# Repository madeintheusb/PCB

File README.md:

# PCB
Eagle Cad PCB developed for MadeInThsUSB

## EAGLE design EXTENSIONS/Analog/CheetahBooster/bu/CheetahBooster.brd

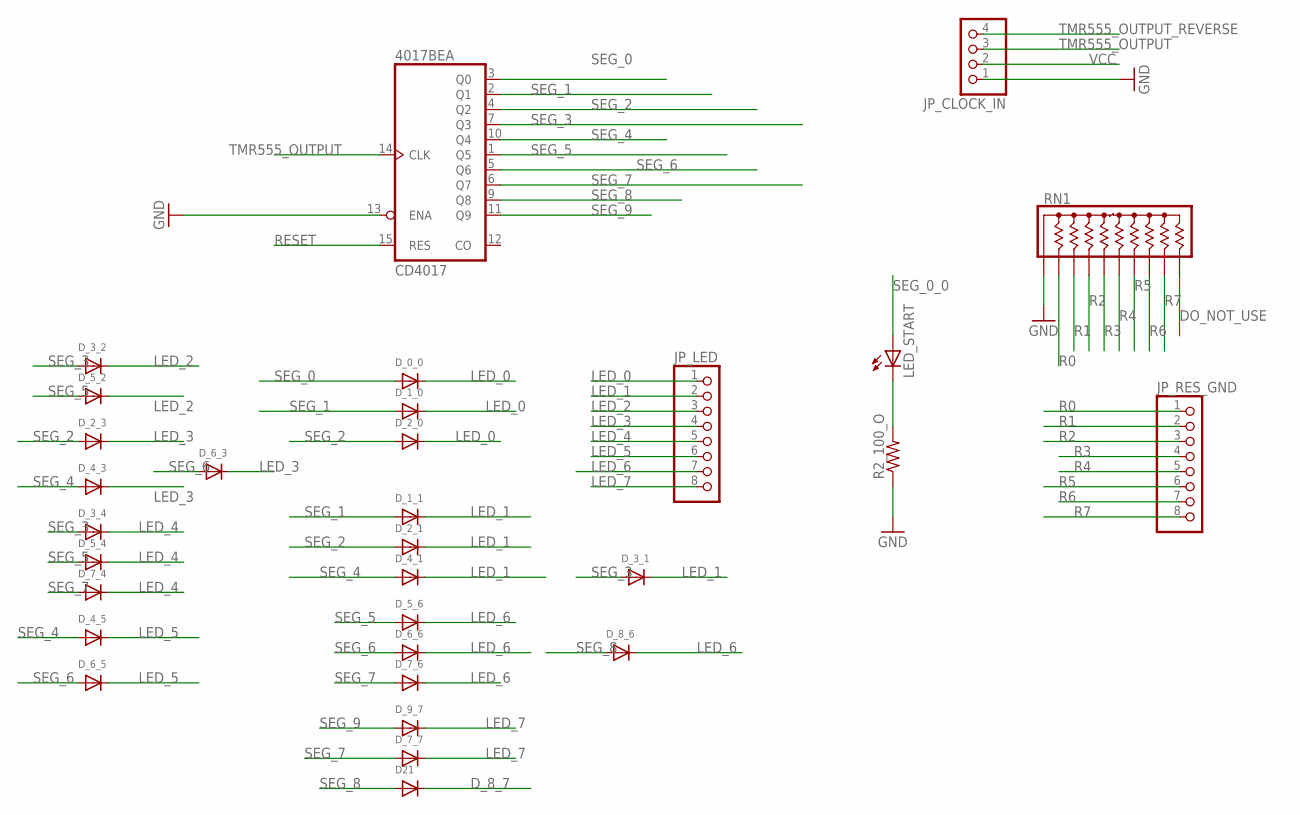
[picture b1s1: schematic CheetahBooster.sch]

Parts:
4017BE: CD4017; DIL16
D21: DIODESMA; SMADIODE
D_0_0, D_1_0, D_1_1, D_2_0, D_2_1, D_2_3, D_3_1, D_3_2, D_3_4, D_4_1, D_4_3, D_4_5, D_5_2, D_5_4, D_5_6, D_6_3, D_6_5, D_6_6, D_7_4, D_7_6, D_7_7, D_8_6, D_9_7: DIODESMA; SMADIODE
JP_CLOCK_IN: PINHD-1X4; 1X04
JP_LED: PINHD-1X8; 1X08
JP_RES_GND: PINHD-1X8; 1X08
LED_START: LEDSMT1206; 1206
R2_100_O: R-US_R1206; R1206
RN1: 4610X; SIP10

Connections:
DO_NOT_USE: RN1.10
D_8_7: D21.C
GND: 4017BE.8 (GND), 4017BE.13 (ENA), JP_CLOCK_IN.1, R2_100_O.1, RN1.1
LED_0: D_0_0.C, D_1_0.C, D_2_0.C, JP_LED.1
LED_1: D_1_1.C, D_2_1.C, D_3_1.C, D_4_1.C, JP_LED.2
LED_2: D_3_2.C, D_5_2.C, JP_LED.3
LED_3: D_2_3.C, D_4_3.C, D_6_3.C, JP_LED.4
LED_4: D_3_4.C, D_5_4.C, D_7_4.C, JP_LED.5
LED_5: D_4_5.C, D_6_5.C, JP_LED.6
LED_6: D_5_6.C, D_6_6.C, D_7_6.C, D_8_6.C, JP_LED.7
LED_7: D_7_7.C, D_9_7.C, JP_LED.8
unnamed: LED_START.C, R2_100_O.2
R0: JP_RES_GND.1, RN1.2
R1: JP_RES_GND.2, RN1.3
R2: JP_RES_GND.3, RN1.4
R3: JP_RES_GND.4, RN1.5
R4: JP_RES_GND.5, RN1.6
R5: JP_RES_GND.6, RN1.7
R6: JP_RES_GND.7, RN1.8
R7: JP_RES_GND.8, RN1.9
RESET: 4017BE.15 (RES)
SEG_0: 4017BE.3 (Q0), D_0_0.A
SEG_0_0: LED_START.A
SEG_1: 4017BE.2 (Q1), D_1_0.A, D_1_1.A
SEG_2: 4017BE.4 (Q2), D_2_0.A, D_2_1.A, D_2_3.A
SEG_3: 4017BE.7 (Q3), D_3_1.A, D_3_2.A, D_3_4.A
SEG_4: 4017BE.10 (Q4), D_4_1.A, D_4_3.A, D_4_5.A
SEG_5: 4017BE.1 (Q5), D_5_2.A, D_5_4.A, D_5_6.A
SEG_6: 4017BE.5 (Q6), D_6_3.A, D_6_5.A, D_6_6.A
SEG_7: 4017BE.6 (Q7), D_7_4.A, D_7_6.A, D_7_7.A
SEG_8: 4017BE.9 (Q8), D21.A, D_8_6.A
SEG_9: 4017BE.11 (Q9), D_9_7.A
TMR555_OUTPUT: 4017BE.14 (CLK), JP_CLOCK_IN.3
TMR555_OUTPUT_REVERSE: JP_CLOCK_IN.4
VCC: 4017BE.16 (VCC), JP_CLOCK_IN.2

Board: 2 copper layers, 31 parts (0 on the bottom side), 30 nets, no tracks yet.

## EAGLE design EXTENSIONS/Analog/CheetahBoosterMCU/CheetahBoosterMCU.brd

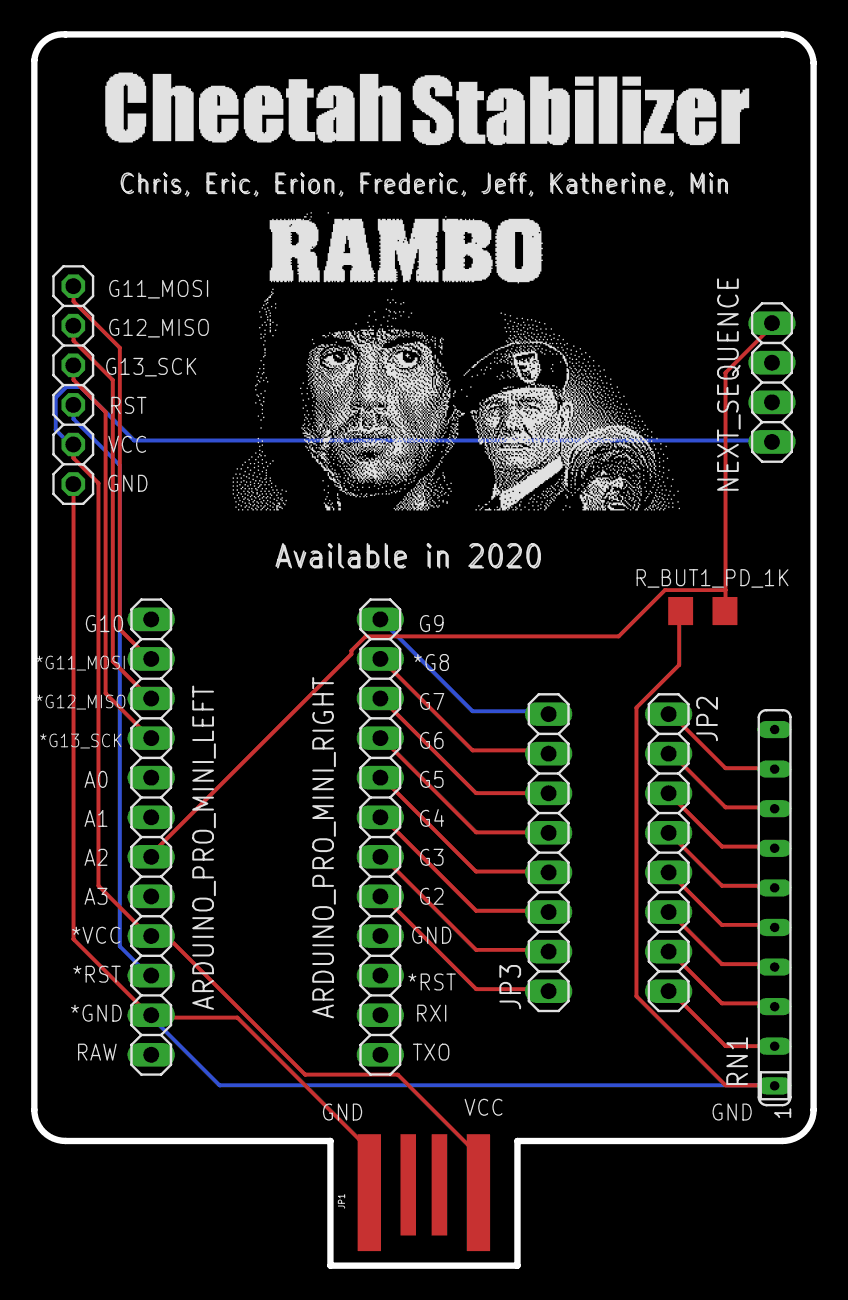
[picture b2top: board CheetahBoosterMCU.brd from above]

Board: 2 copper layers, 50.0 x 79.0 mm, 9 parts (0 on the bottom side), 23 nets.

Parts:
ARDUINO_PRO_MINI_LEFT: 1X12
ARDUINO_PRO_MINI_RIGHT: 1X12
JP1: USBPCB; USB-A-PCB
JP2, JP3: 1X08
JP_PROGRAMMING: 1X06
NEXT_SEQUENCE: 1X04
RN1: SIP10
R_BUT1_PD_1K: R1206

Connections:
A2: ARDUINO_PRO_MINI_LEFT.7, NEXT_SEQUENCE.4, R_BUT1_PD_1K.2
G2: ARDUINO_PRO_MINI_RIGHT.8, JP3.1
G3: ARDUINO_PRO_MINI_RIGHT.7, JP3.2
G4: ARDUINO_PRO_MINI_RIGHT.6, JP3.3
G5: ARDUINO_PRO_MINI_RIGHT.5, JP3.4
G6: ARDUINO_PRO_MINI_RIGHT.4, JP3.5
G7: ARDUINO_PRO_MINI_RIGHT.3, JP3.6
G8: ARDUINO_PRO_MINI_RIGHT.2, JP3.7
G9: ARDUINO_PRO_MINI_RIGHT.1, JP3.8
G11_MOSI: ARDUINO_PRO_MINI_LEFT.2, JP_PROGRAMMING.6
G12_MISO: ARDUINO_PRO_MINI_LEFT.3, JP_PROGRAMMING.5
G13_SCK: ARDUINO_PRO_MINI_LEFT.4, JP_PROGRAMMING.4
GND: ARDUINO_PRO_MINI_LEFT.11, JP1.GND, JP_PROGRAMMING.1, RN1.1, R_BUT1_PD_1K.1
R0: JP2.1, RN1.9
R1: JP2.2, RN1.8
R2: JP2.3, RN1.7
R3: JP2.4, RN1.6
R4: JP2.5, RN1.5
R5: JP2.6, RN1.4
R6: JP2.7, RN1.3
R7: JP2.8, RN1.2
RST: ARDUINO_PRO_MINI_LEFT.10, JP_PROGRAMMING.3
VCC: ARDUINO_PRO_MINI_LEFT.9, JP1.5V, JP_PROGRAMMING.2, NEXT_SEQUENCE.1

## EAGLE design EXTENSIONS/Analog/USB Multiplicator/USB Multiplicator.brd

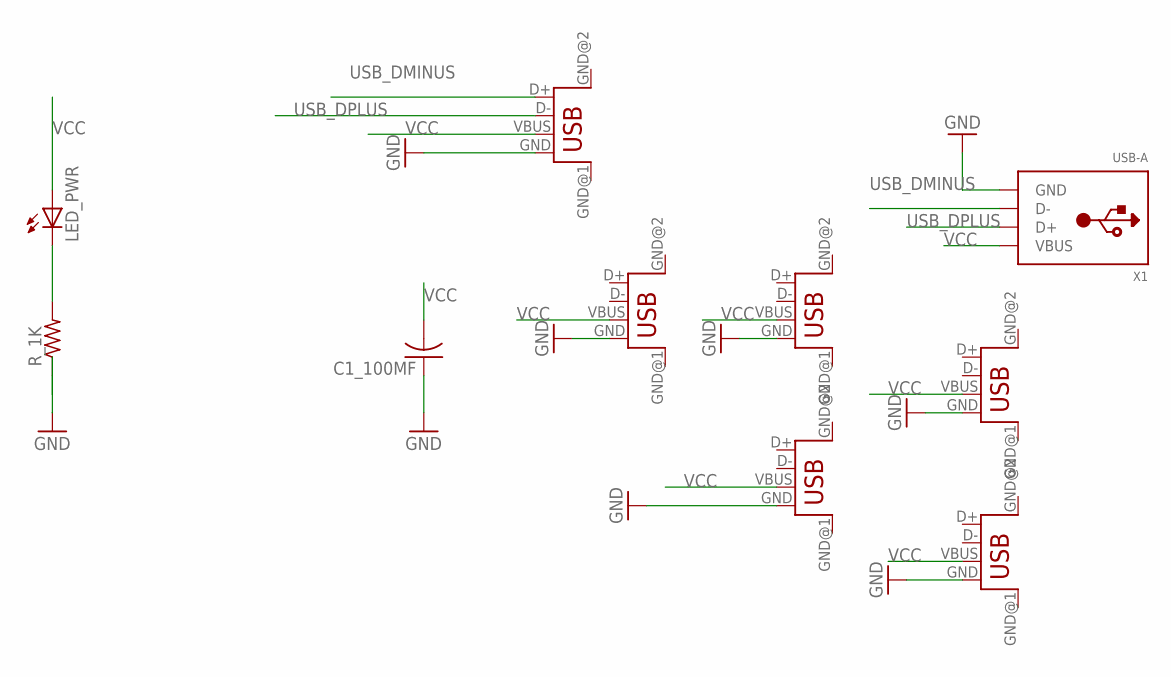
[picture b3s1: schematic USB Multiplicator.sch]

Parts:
C1_100MF: C-US025-030X050; C025-030X050
LED_PWR: LEDSMT1206; 1206
R_1K: R-US_R1206; R1206
USB_OUT_2, USB_OUT_3, USB_OUT_4, USB_OUT_5, USB_OUT_6: USB; USB-FEMALE-A-PTH
USB_OUT_WITH_DATA_1: USB; USB-FEMALE-A-PTH
X1: USB-A; MOLEX_480371000

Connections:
GND: C1_100MF.1, R_1K.1, USB_OUT_2.GND, USB_OUT_3.GND, USB_OUT_4.GND, USB_OUT_5.GND, USB_OUT_6.GND, USB_OUT_WITH_DATA_1.GND, X1.4 (GND)
unnamed: LED_PWR.C, R_1K.2
USB_DMINUS: USB_OUT_WITH_DATA_1.D+, X1.2 (D-)
USB_DPLUS: USB_OUT_WITH_DATA_1.D-, X1.3 (D+)
VCC: C1_100MF.2, LED_PWR.A, USB_OUT_2.VBUS, USB_OUT_3.VBUS, USB_OUT_4.VBUS, USB_OUT_5.VBUS, USB_OUT_6.VBUS, USB_OUT_WITH_DATA_1.VBUS, X1.1 (VBUS)

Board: 2 copper layers, 10 parts (0 on the bottom side), 5 nets, no tracks yet.

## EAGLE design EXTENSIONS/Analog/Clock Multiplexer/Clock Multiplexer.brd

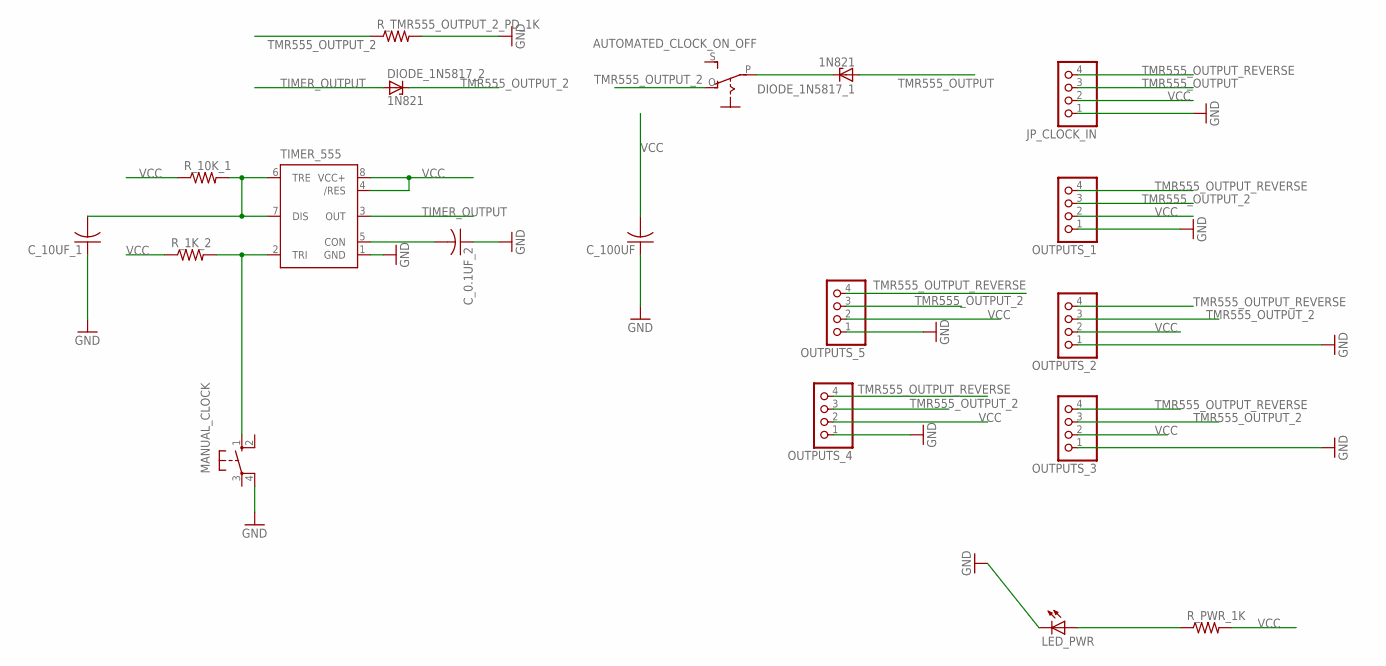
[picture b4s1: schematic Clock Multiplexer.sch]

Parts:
AUTOMATED_CLOCK_ON_OFF: EG1218S; EG1218
C_0.1UF_2, C_10UF_1: C-USC1206; C1206
C_100UF: C-US025-030X050; C025-030X050
DIODE_1N5817_1, DIODE_1N5817_2: 1N821; DO35Z10
JP_CLOCK_IN: PINHD-1X4; 1X04
LED_PWR: LEDSMT1206; 1206
MANUAL_CLOCK: 10-XX; B3F-10XX
OUTPUTS_1, OUTPUTS_2, OUTPUTS_3, OUTPUTS_4, OUTPUTS_5: PINHD-1X4; 1X04
R_1K_2, R_10K_1: R-US_R1206; R1206
R_PWR_1K: R-US_R1206; R1206
R_TMR555_OUTPUT_2_PD_1K: R-US_R1206; R1206
TIMER_555: NE555D; SO08

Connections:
GND: C_0.1UF_2.1, C_10UF_1.1, C_100UF.1, JP_CLOCK_IN.1, LED_PWR.C, MANUAL_CLOCK.4 (P1), OUTPUTS_1.1, OUTPUTS_2.1, OUTPUTS_3.1, OUTPUTS_4.1, OUTPUTS_5.1, R_TMR555_OUTPUT_2_PD_1K.2, TIMER_555.1 (GND)
unnamed: LED_PWR.A, R_PWR_1K.1
unnamed: AUTOMATED_CLOCK_ON_OFF.P, DIODE_1N5817_1.C
unnamed: C_10UF_1.2, R_10K_1.2, TIMER_555.6 (TRE), TIMER_555.7 (DIS)
unnamed: C_0.1UF_2.2, TIMER_555.5 (CON)
unnamed: MANUAL_CLOCK.1 (S), R_1K_2.2, TIMER_555.2 (TRI)
TIMER_OUTPUT: DIODE_1N5817_2.A, TIMER_555.3 (OUT)
TMR555_OUTPUT: DIODE_1N5817_1.A, JP_CLOCK_IN.3
TMR555_OUTPUT_2: AUTOMATED_CLOCK_ON_OFF.O, DIODE_1N5817_2.C, OUTPUTS_1.3, OUTPUTS_2.3, OUTPUTS_3.3, OUTPUTS_4.3, OUTPUTS_5.3, R_TMR555_OUTPUT_2_PD_1K.1
TMR555_OUTPUT_REVERSE: JP_CLOCK_IN.4, OUTPUTS_1.4, OUTPUTS_2.4, OUTPUTS_3.4, OUTPUTS_4.4, OUTPUTS_5.4
VCC: C_100UF.2, JP_CLOCK_IN.2, OUTPUTS_1.2, OUTPUTS_2.2, OUTPUTS_3.2, OUTPUTS_4.2, OUTPUTS_5.2, R_1K_2.1, R_10K_1.1, R_PWR_1K.2, TIMER_555.4 (/RES), TIMER_555.8 (VCC+)

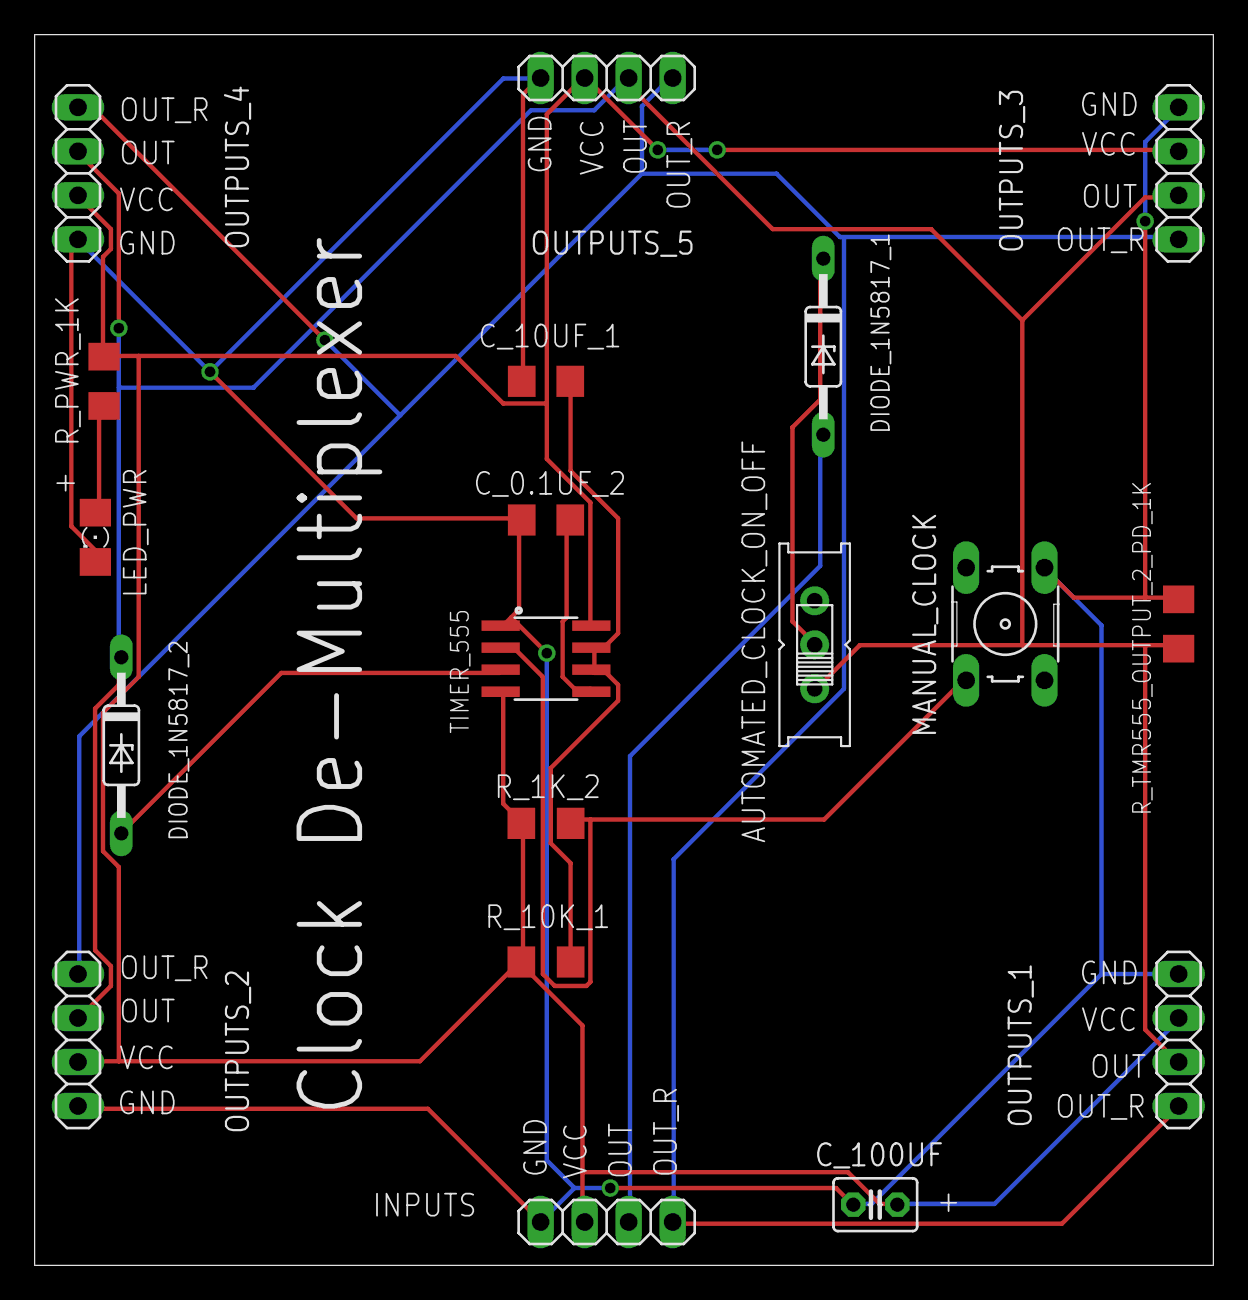
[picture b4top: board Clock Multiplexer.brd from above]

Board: 2 copper layers, 68.0 x 71.0 mm, 19 parts (0 on the bottom side), 11 nets.

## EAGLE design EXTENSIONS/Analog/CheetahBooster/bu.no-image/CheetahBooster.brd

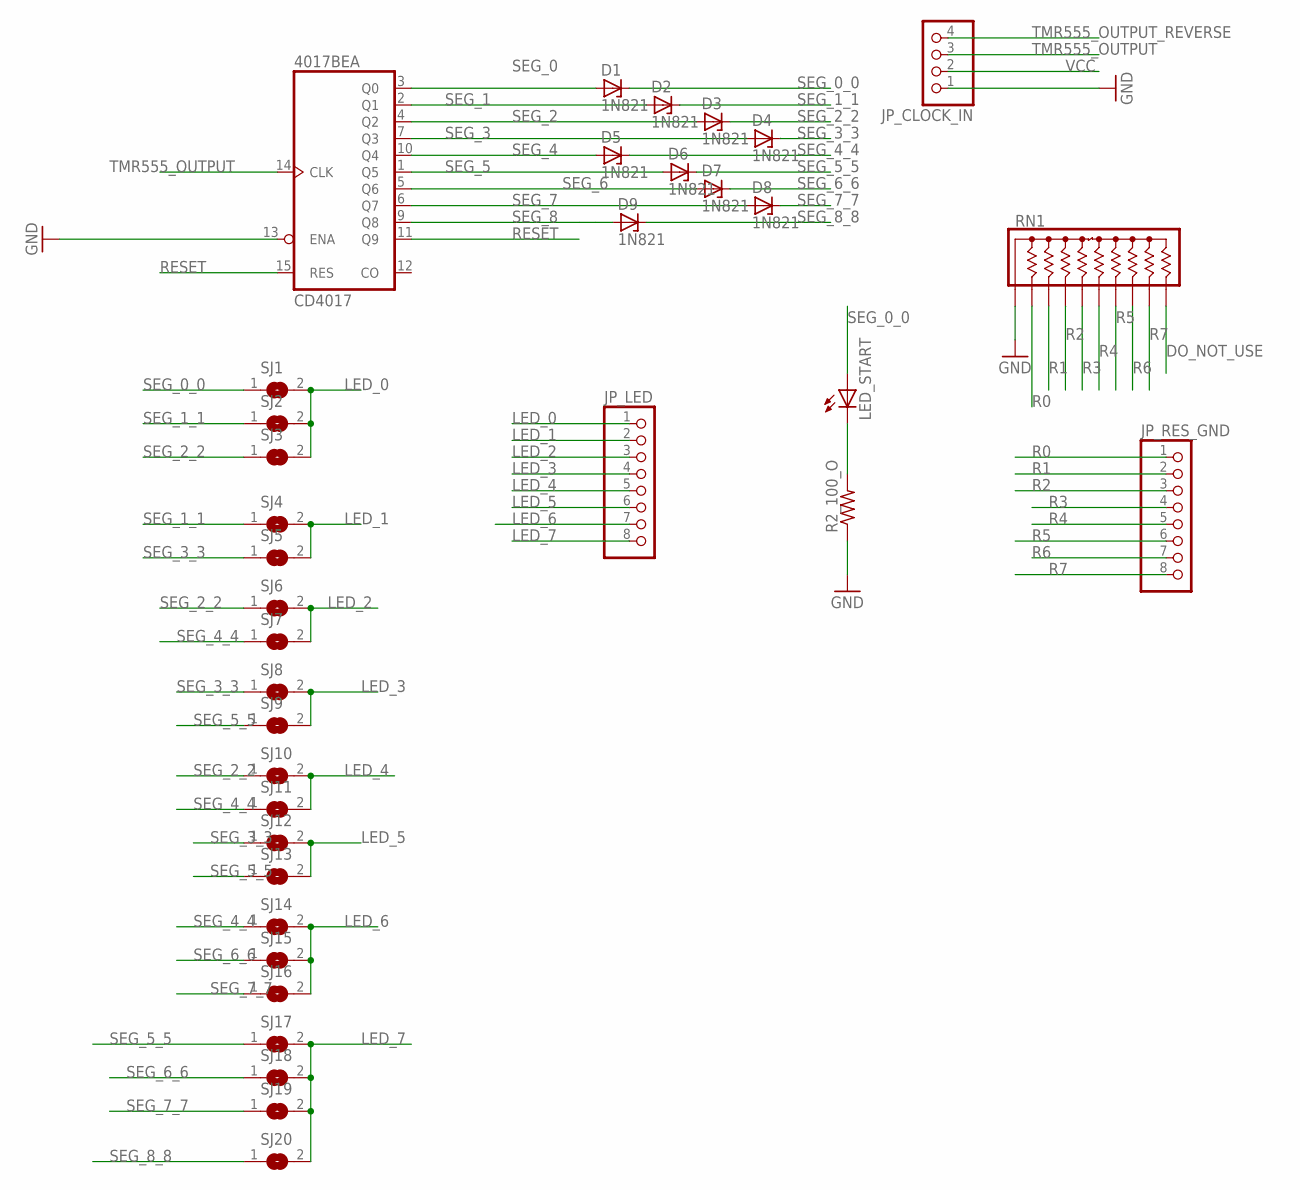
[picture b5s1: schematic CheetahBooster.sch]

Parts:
4017BE: CD4017; DIL16
D1, D2, D3, D4, D5, D6, D7, D8, D9: 1N821; DO35Z10
JP_CLOCK_IN: PINHD-1X4; 1X04
JP_LED: PINHD-1X8; 1X08
JP_RES_GND: PINHD-1X8; 1X08
LED_START: LEDSMT1206; 1206
R2_100_O: R-US_R1206; R1206
RN1: 4610X; SIP10
SJ1, SJ2, SJ3, SJ4, SJ5, SJ6, SJ7, SJ8, SJ9, SJ10, SJ11, SJ12, SJ13, SJ14, SJ15, SJ16, SJ17, SJ18, SJ19, SJ20: SOLDERJUMPER; SOLDERJUMPER_ARROW_NOPASTE

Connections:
DO_NOT_USE: RN1.10
GND: 4017BE.8 (GND), 4017BE.13 (ENA), JP_CLOCK_IN.1, R2_100_O.1, RN1.1
LED_0: JP_LED.1, SJ1.2, SJ2.2, SJ3.2
LED_1: JP_LED.2, SJ4.2, SJ5.2
LED_2: JP_LED.3, SJ6.2, SJ7.2
LED_3: JP_LED.4, SJ8.2, SJ9.2
LED_4: JP_LED.5, SJ10.2, SJ11.2
LED_5: JP_LED.6, SJ12.2, SJ13.2
LED_6: JP_LED.7, SJ14.2, SJ15.2, SJ16.2
LED_7: JP_LED.8, SJ17.2, SJ18.2, SJ19.2, SJ20.2
unnamed: LED_START.C, R2_100_O.2
R0: JP_RES_GND.1, RN1.2
R1: JP_RES_GND.2, RN1.3
R2: JP_RES_GND.3, RN1.4
R3: JP_RES_GND.4, RN1.5
R4: JP_RES_GND.5, RN1.6
R5: JP_RES_GND.6, RN1.7
R6: JP_RES_GND.7, RN1.8
R7: JP_RES_GND.8, RN1.9
RESET: 4017BE.11 (Q9), 4017BE.15 (RES)
SEG_0: 4017BE.3 (Q0), D1.A
SEG_0_0: D1.C, LED_START.A, SJ1.1
SEG_1: 4017BE.2 (Q1), D2.A
SEG_1_1: D2.C, SJ2.1, SJ4.1
SEG_2: 4017BE.4 (Q2), D3.A
SEG_2_2: D3.C, SJ3.1, SJ6.1, SJ10.1
SEG_3: 4017BE.7 (Q3), D4.A
SEG_3_3: D4.C, SJ5.1, SJ8.1, SJ12.1
SEG_4: 4017BE.10 (Q4), D5.A
SEG_4_4: D5.C, SJ7.1, SJ11.1, SJ14.1
SEG_5: 4017BE.1 (Q5), D6.A
SEG_5_5: D6.C, SJ9.1, SJ13.1, SJ17.1
SEG_6: 4017BE.5 (Q6), D7.A
SEG_6_6: D7.C, SJ15.1, SJ18.1
SEG_7: 4017BE.6 (Q7), D8.A
SEG_7_7: D8.C, SJ16.1, SJ19.1
SEG_8: 4017BE.9 (Q8), D9.A
SEG_8_8: D9.C, SJ20.1
TMR555_OUTPUT: 4017BE.14 (CLK), JP_CLOCK_IN.3
TMR555_OUTPUT_REVERSE: JP_CLOCK_IN.4
VCC: 4017BE.16 (VCC), JP_CLOCK_IN.2

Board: 2 copper layers, 36 parts (0 on the bottom side), 39 nets, no tracks yet.

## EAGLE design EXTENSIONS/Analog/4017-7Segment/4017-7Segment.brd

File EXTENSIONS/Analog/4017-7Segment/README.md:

g f G a b            4017B Pin
                       
                        _____
    a               f 5|1   16|Vcc  
    _               b 1|2   15|Rst
f  | | b            a 0|3   14|Clk
    -g              c 2|4   13|Clk I 
 e | | c            g 6|5   12|Cry 
    -             Rst 7|6   11|9
    d               d 3|7   10|4 e
                      G|8    9|8
e d G c dp              _____

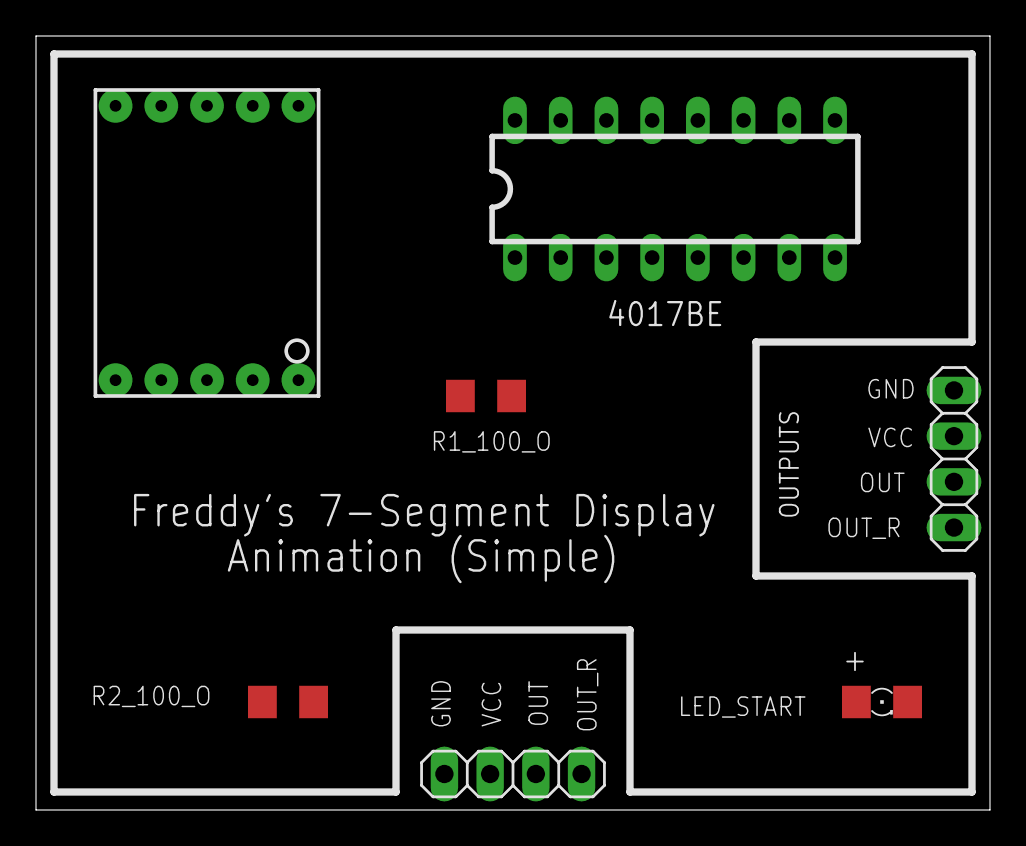
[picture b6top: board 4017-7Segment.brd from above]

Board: 2 copper layers, 53.0 x 43.0 mm, 7 parts (0 on the bottom side), 13 nets, no tracks yet.

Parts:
4017BE: CD4017; DIL16
JP_CLOCK_IN: 1X04
LED_START: 1206
OUTPUTS: 1X04
R1_100_O, R2_100_O: R1206
U$1: 7-SEGMENT-DISPLAYPTH; 7-SEGMENT-DISPLAY

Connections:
GND: 4017BE.8, 4017BE.13, JP_CLOCK_IN.1, OUTPUTS.1, R1_100_O.1, R2_100_O.1
unnamed: LED_START.C, R2_100_O.2
unnamed: R1_100_O.2, U$1.8
RESET: 4017BE.5, 4017BE.15
SEG_A: 4017BE.3, LED_START.A, U$1.7
SEG_B: 4017BE.2, U$1.6
SEG_C: 4017BE.4, U$1.4
SEG_D: 4017BE.7, U$1.2
SEG_E: 4017BE.10, U$1.1
SEG_F: 4017BE.1, U$1.9
TMR555_OUTPUT: 4017BE.14, JP_CLOCK_IN.3, OUTPUTS.3
TMR555_OUTPUT_REVERSE: JP_CLOCK_IN.4, OUTPUTS.4
VCC: 4017BE.16, JP_CLOCK_IN.2, OUTPUTS.2

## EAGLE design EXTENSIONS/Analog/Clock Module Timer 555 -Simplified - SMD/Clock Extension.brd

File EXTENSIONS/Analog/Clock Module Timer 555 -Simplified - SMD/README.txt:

http://www.ohmslawcalculator.com/555-astable-calculator

Timer NE555 SOP
Capacitor 10 uF SMD 1206
R1 1k 1206
R2 100k Blue Pot From China

at 100k Pot Frequency is 0.7/S
at 20 Ohm Pot Frequency is 120/S

Timer 555 pin
https://www.google.com/imgres?imgurl=http%3A%2F%2Fwww.hobbytronics.co.uk%2Fimage%2Fcache%2Fdata%2F555-timer-pinout-500x500.jpg&imgrefurl=http%3A%2F%2Fwww.hobbytronics.co.uk%2F555-timer-ic-soic8&docid=phPU6GICSihb0M&tbnid=dgrUePlWMjdoEM%3A&vet=10ahUKEwjU_o-7kr7mAhVqdt8KHc7vCX8QMwjZAighMCE..i&w=500&h=500&bih=657&biw=1280&q=timer%20555%20sop%208&ved=0ahUKEwjU_o-7kr7mAhVqdt8KHc7vCX8QMwjZAighMCE&iact=mrc&uact=8

DIMENSION TO SOLDER ON TOP OF ANOTHER BOARD

20 cm width
- Bottom 2 pins attach at 10cm,10cm  in the middle
- Top 4 pins attach at    10cm,30cm in the middle
			  xxxx,20cm up

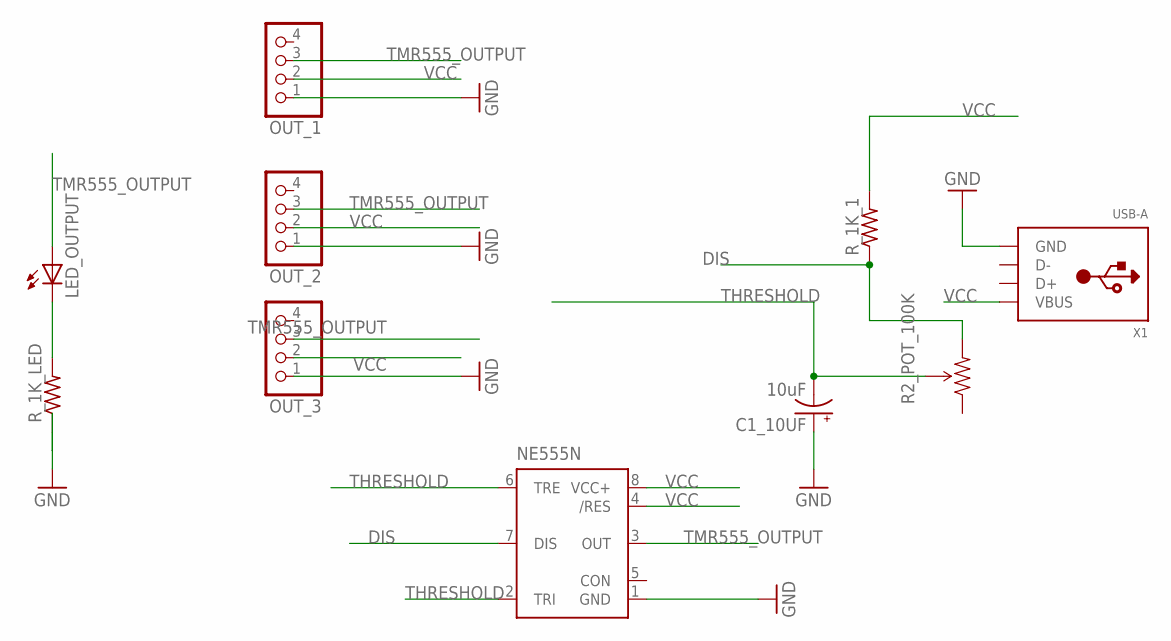
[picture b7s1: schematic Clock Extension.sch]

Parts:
C1_10UF: 10uF; EIA3216
LED_OUTPUT: LEDSMT1206; 1206
NE555N: NE555D; SO08
OUT_1, OUT_2, OUT_3: PINHD-1X4; 1X04
R2_POT_100K: TRIMPOTPTH; TRIM_POT_PTH
R_1K_1, R_1K_LED: R-US_R1206; R1206
X1: USB-A; MOLEX_480371000

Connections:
DIS: NE555N.7 (DIS), R2_POT_100K.3 (CW), R_1K_1.1
GND: C1_10UF.A (+), NE555N.1 (GND), OUT_1.1, OUT_2.1, OUT_3.1, R_1K_LED.1, X1.4 (GND)
unnamed: LED_OUTPUT.C, R_1K_LED.2
THRESHOLD: C1_10UF.C (-), NE555N.2 (TRI), NE555N.6 (TRE), R2_POT_100K.2 (WIPER)
TMR555_OUTPUT: LED_OUTPUT.A, NE555N.3 (OUT), OUT_1.3, OUT_2.3, OUT_3.3
VCC: NE555N.4 (/RES), NE555N.8 (VCC+), OUT_1.2, OUT_2.2, OUT_3.2, R_1K_1.2, X1.1 (VBUS)

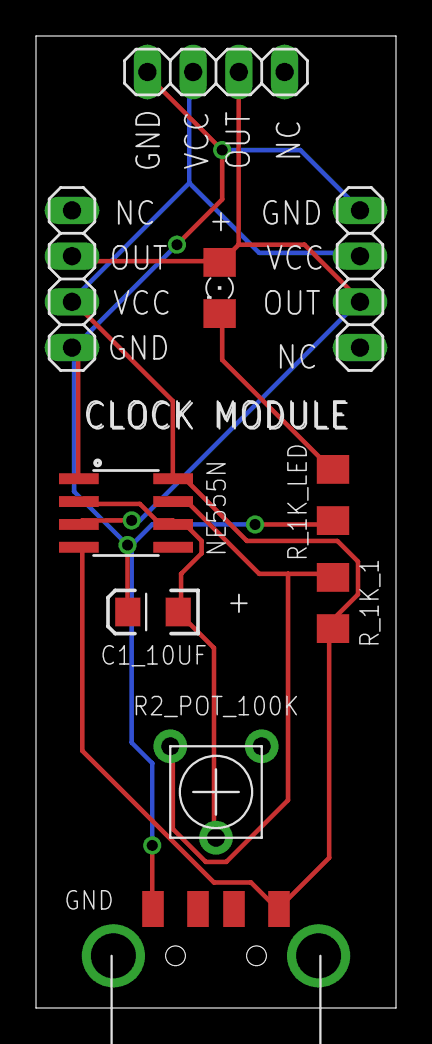
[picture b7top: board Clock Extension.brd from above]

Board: 2 copper layers, 20.0 x 54.0 mm, 10 parts (0 on the bottom side), 6 nets.

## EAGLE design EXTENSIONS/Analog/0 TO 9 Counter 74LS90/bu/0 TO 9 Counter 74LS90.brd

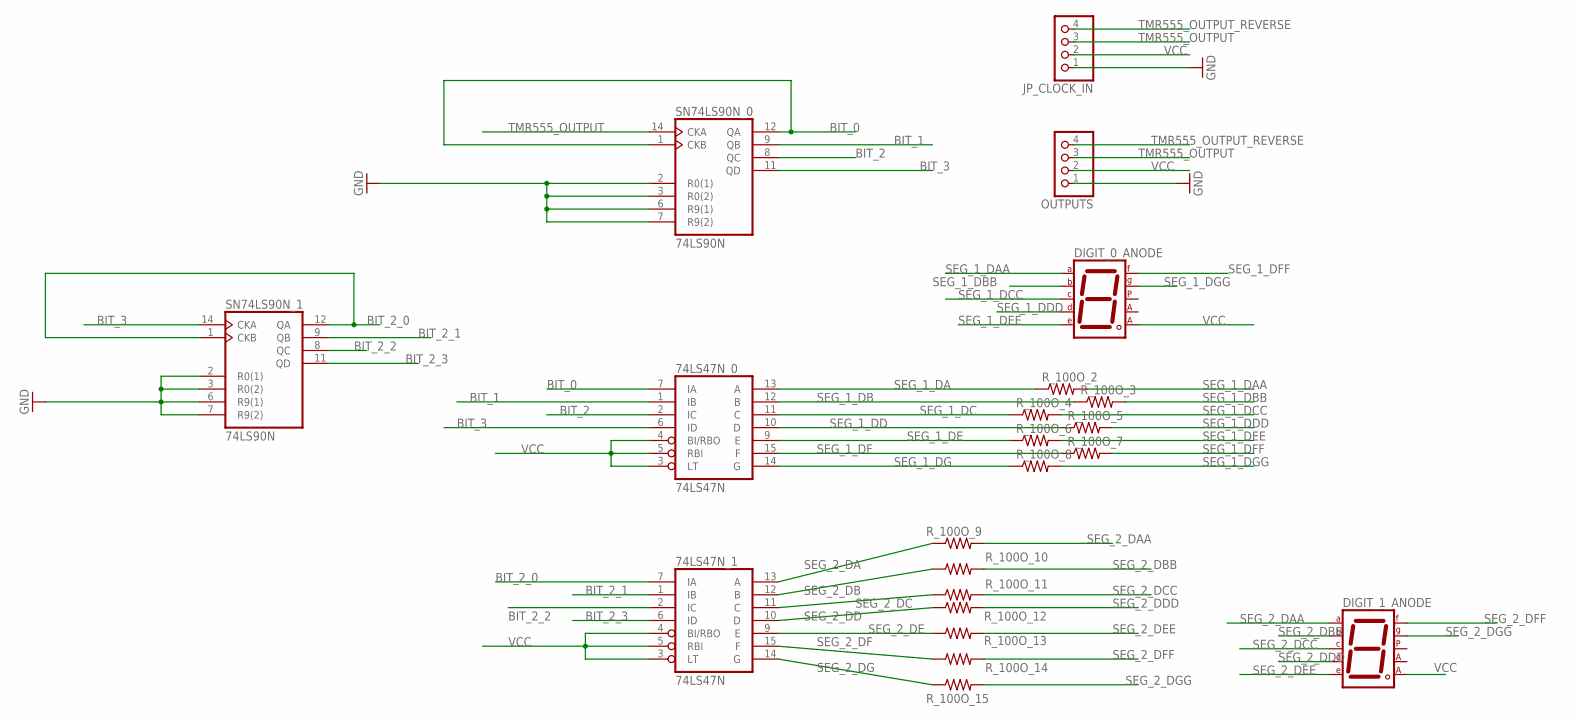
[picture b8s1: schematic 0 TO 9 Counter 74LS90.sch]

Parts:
74LS47N_0, 74LS47N_1: 74LS47N; DIL16
DIGIT_0_ANODE, DIGIT_1_ANODE: 7SEG-CA; 7SEG-13
JP_CLOCK_IN: PINHD-1X4; 1X04
OUTPUTS: PINHD-1X4; 1X04
R_100O_2, R_100O_3, R_100O_4, R_100O_5, R_100O_6, R_100O_7, R_100O_8, R_100O_9, R_100O_10, R_100O_11, R_100O_12, R_100O_13, R_100O_14, R_100O_15: R-US_R1206; R1206
SN74LS90N_0, SN74LS90N_1: 74LS90N; DIL14

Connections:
BIT_0: 74LS47N_0.7 (IA), SN74LS90N_0.1 (CKB), SN74LS90N_0.12 (QA)
BIT_1: 74LS47N_0.1 (IB), SN74LS90N_0.9 (QB)
BIT_2: 74LS47N_0.2 (IC), SN74LS90N_0.8 (QC)
BIT_2_0: 74LS47N_1.7 (IA), SN74LS90N_1.1 (CKB), SN74LS90N_1.12 (QA)
BIT_2_1: 74LS47N_1.1 (IB), SN74LS90N_1.9 (QB)
BIT_2_2: 74LS47N_1.2 (IC), SN74LS90N_1.8 (QC)
BIT_2_3: 74LS47N_1.6 (ID), SN74LS90N_1.11 (QD)
BIT_3: 74LS47N_0.6 (ID), SN74LS90N_0.11 (QD), SN74LS90N_1.14 (CKA)
GND: 74LS47N_0.8 (GND), 74LS47N_1.8 (GND), JP_CLOCK_IN.1, OUTPUTS.1, SN74LS90N_0.2 (R0(1)), SN74LS90N_0.3 (R0(2)), SN74LS90N_0.6 (R9(1)), SN74LS90N_0.7 (R9(2)), SN74LS90N_0.10 (GND), SN74LS90N_1.2 (R0(1)), SN74LS90N_1.3 (R0(2)), SN74LS90N_1.6 (R9(1)), SN74LS90N_1.7 (R9(2)), SN74LS90N_1.10 (GND)
SEG_1_DA: 74LS47N_0.13 (A), R_100O_2.1
SEG_1_DAA: DIGIT_0_ANODE.7 (A), R_100O_2.2
SEG_1_DB: 74LS47N_0.12 (B), R_100O_3.1
SEG_1_DBB: DIGIT_0_ANODE.6 (B), R_100O_3.2
SEG_1_DC: 74LS47N_0.11 (C), R_100O_4.1
SEG_1_DCC: DIGIT_0_ANODE.4 (C), R_100O_4.2
SEG_1_DD: 74LS47N_0.10 (D), R_100O_5.1
SEG_1_DDD: DIGIT_0_ANODE.2 (D), R_100O_5.2
SEG_1_DE: 74LS47N_0.9 (E), R_100O_6.1
SEG_1_DEE: DIGIT_0_ANODE.1 (E), R_100O_6.2
SEG_1_DF: 74LS47N_0.15 (F), R_100O_7.1
SEG_1_DFF: DIGIT_0_ANODE.9 (F), R_100O_7.2
SEG_1_DG: 74LS47N_0.14 (G), R_100O_8.1
SEG_1_DGG: DIGIT_0_ANODE.10 (G), R_100O_8.2
SEG_2_DA: 74LS47N_1.13 (A), R_100O_9.1
SEG_2_DAA: DIGIT_1_ANODE.7 (A), R_100O_9.2
SEG_2_DB: 74LS47N_1.12 (B), R_100O_10.1
SEG_2_DBB: DIGIT_1_ANODE.6 (B), R_100O_10.2
SEG_2_DC: 74LS47N_1.11 (C), R_100O_11.1
SEG_2_DCC: DIGIT_1_ANODE.4 (C), R_100O_11.2
SEG_2_DD: 74LS47N_1.10 (D), R_100O_12.1
SEG_2_DDD: DIGIT_1_ANODE.2 (D), R_100O_12.2
SEG_2_DE: 74LS47N_1.9 (E), R_100O_13.1
SEG_2_DEE: DIGIT_1_ANODE.1 (E), R_100O_13.2
SEG_2_DF: 74LS47N_1.15 (F), R_100O_14.1
SEG_2_DFF: DIGIT_1_ANODE.9 (F), R_100O_14.2
SEG_2_DG: 74LS47N_1.14 (G), R_100O_15.1
SEG_2_DGG: DIGIT_1_ANODE.10 (G), R_100O_15.2
TMR555_OUTPUT: JP_CLOCK_IN.3, OUTPUTS.3, SN74LS90N_0.14 (CKA)
TMR555_OUTPUT_REVERSE: JP_CLOCK_IN.4, OUTPUTS.4
VCC: 74LS47N_0.3 (LT), 74LS47N_0.4 (BI/RBO), 74LS47N_0.5 (RBI), 74LS47N_0.16 (VCC), 74LS47N_1.3 (LT), 74LS47N_1.4 (BI/RBO), 74LS47N_1.5 (RBI), 74LS47N_1.16 (VCC), DIGIT_0_ANODE.8 (CA2), DIGIT_1_ANODE.8 (CA2), JP_CLOCK_IN.2, OUTPUTS.2, SN74LS90N_0.5 (VCC), SN74LS90N_1.5 (VCC)

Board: 2 copper layers, 22 parts (0 on the bottom side), 40 nets, no tracks yet.

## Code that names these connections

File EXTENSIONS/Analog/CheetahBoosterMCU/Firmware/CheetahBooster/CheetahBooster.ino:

#include <fArduino.h>
#include "CheetahBooster.h"

#define DEBUG_ANIMATION 0
Led _onBoardLed(LED_BUILTIN);

#define LED_0 2
#define LED_1 3
#define LED_2 4
#define LED_3 5
#define LED_4 6
#define LED_5 7
#define LED_6 8
#define LED_7 9
#define LED_MIN LED_0
#define LED_MAX LED_7

#define ANIMATION_CHANGE_BUTTON_ANALOG_PIN 2 // Need a Pull down resitor

#define MIN_ANIMATION_INDEX 0
#define MAX_ANIMATION_INDEX (4-1)

#define WAIT 150

int _currentAnimation = MIN_ANIMATION_INDEX; // We have 4 different types of animation which repeat
int _animationRepeatCounter = 0; // Count the repeat of the current animation
bool _repeatAnimation = true; // When false we stay on the current animation, can be changed with the button
#define ANIMATION_COUNTER_MAX 4 // After each 16 instance of an animation we move to the next one

bool AnalogButtonPressed()
{
	return analogRead(ANIMATION_CHANGE_BUTTON_ANALOG_PIN) > 512;
}

bool IsAnimationChangeButtonPressed()
{
	bool pressed = AnalogButtonPressed();
	if (pressed) { // Wait for button to be released
		Board.Trace("IsAnimationChangeButtonPressed");
		AllOn();
		while (AnalogButtonPressed())
		{
			delay(200);
		}
		AllOff();
	}
	return pressed;
}

void NextAnimation() {

	_currentAnimation += 1;
	if (_currentAnimation > MAX_ANIMATION_INDEX)
		_currentAnimation = MIN_ANIMATION_INDEX;
}

bool CheckForUserAction() {

	_onBoardLed.Blink(); // Takes care of animation the on board led on/off animation

	if (IsAnimationChangeButtonPressed())
	{		
		_repeatAnimation = !_repeatAnimation;
		return true; // Notify change of state
	}
	return false;
}

void InitPins()
{
	for (int p = LED_MIN; p <= LED_7; p++) // all off
		pinMode(p, OUTPUT);

	pinMode(LED_BUILTIN, OUTPUT);
}

void Sequence(int count, int pins[])
{
	AllOff();

	for (int p = 0; p < count; p++)
	{
		int pin = pins[p] + LED_MIN;
		digitalWrite(pin, HIGH);
	}

	int wait = WAIT;
	if (DEBUG_ANIMATION) wait *= 3;
	delay(wait - (count * 15));
}

void AllOff()
{
	for (int p = LED_MIN; p <= LED_7; p++)
		digitalWrite(p, LOW);
}

void AllOn()
{
	for (int p = LED_MIN; p <= LED_7; p++)
		digitalWrite(p, HIGH);
}

void Sequence(int pin0)
{
	if (pin0 == -1) {
		int arr[] = { pin0 };
		Sequence(0, arr); // Only clear all
	}
	else
	{
		int arr[] = { pin0 };
		Sequence(1, arr);
	}
}

void Sequence(int pin0, int pin1)
{
	int arr[] = { pin0, pin1 };
	Sequence(2, arr);
}

void Sequence(int pin0, int pin1, int pin2)
{
	int arr[] = { pin0, pin1, pin2 };
	Sequence(3, arr);
}

void Sequence(int pin0, int pin1, int pin2, int pin3)
{
	int arr[] = { pin0, pin1, pin2, pin3 };
	Sequence(4, arr);
}

void Sequence(int pin0, int pin1, int pin2, int pin3, int pin4)
{
	int arr[] = { pin0, pin1, pin2, pin3, pin4 };
	Sequence(5, arr);
}

void Animation1(bool clearLastStep)
{
	if (CheckForUserAction()) return;
	Sequence(0);
	Sequence(0, 1);
	Sequence(0, 1, 3);
	Sequence(1, 2, 4);
	Sequence(1, 3, 5);
	Sequence(2, 4, 6);
	if (CheckForUserAction()) return;
	Sequence(3, 5, 6);
	Sequence(4, 6, 7);
	Sequence(6, 7);
	Sequence(7);
	if (clearLastStep)
		Sequence(-1);
}

void Animation2(bool clearLastStep)
{
	if (CheckForUserAction()) return;

	Sequence(7);
	Sequence(6, 7);
	Sequence(4, 6, 7);
	Sequence(3, 5, 6);
	Sequence(2, 4, 6);
	if (CheckForUserAction()) return;
	Sequence(1, 3, 5);
	Sequence(1, 2, 4);
	Sequence(0, 1, 3);
	Sequence(0, 1);
	Sequence(0);

	if (clearLastStep)
		Sequence(-1);
}

void Animation3()
{
	Animation1(false);
	if (CheckForUserAction()) return;
	Sequence(7);
	Sequence(6, 7);
	Sequence(4, 6, 7);
	Sequence(3, 5, 6);
	Sequence(2, 4, 6);
	Sequence(1, 3, 5);
	if (CheckForUserAction()) return;
	Sequence(1, 2, 4);
	Sequence(0, 1, 3);
	Sequence(0, 1);
	Sequence(0);
}

void Animation4()
{
	Sequence(0);
	Sequence(0, 2);
	Sequence(0, 2, 4);
	Sequence(0, 2, 4, 6);
	Sequence(1, 3, 5, 7);
	Sequence(2, 4, 6, 7);
	Sequence(5, 6, 7);
	Sequence(6, 7);
	Sequence(7);
	Sequence(-1);
	Sequence(-1);
	Sequence(7);
	if (CheckForUserAction()) return;
	Sequence(6, 7);
	Sequence(5, 6, 7);
	Sequence(2, 4, 6, 7);
	Sequence(1, 3, 5, 7);
	Sequence(0, 2, 4, 6);
	Sequence(0, 2, 4);
	Sequence(0, 1, 2);
	Sequence(0, 1);
	Sequence(0);
	Sequence(-1);
	Sequence(-1);
}

void Animation5()
{
	for (int z = 0; z < 10; z++) {

		int maxSeq = 2;
		for (int i = 0; i < maxSeq; i++) {

			Sequence(0, 2, 4, 6);
			delay(WAIT / (1 + z));
			Sequence(1, 3, 5, 7);
			delay(WAIT / (1 + z));
			if (CheckForUserAction()) return;
		}
	}
}

void setup()
{
	Board.InitializeComputerCommunication(9600, "Starting");
	InitPins();
	for (int i = 0; i < 10; i++) {
		AllOn();
		delay(150 - (i * 10));
		AllOff();
		delay(150 - (i * 10));
	}	
	Sequence(0);
	_onBoardLed.SetBlinkMode(500); // Blink every 1/2 second
	delay(1000);
}

// Add the main program code into the continuous loop() function
void loop()
{
	CheckForUserAction();

	if (_currentAnimation == 0)
		Animation1(true);
	else if (_currentAnimation == 1)
		Animation2(true);
	else if (_currentAnimation == 2)
		Animation3();
	else if (_currentAnimation == 3)
		Animation4();
	
	// If we are in repeat animation mode, we increase the repeat
	if (_repeatAnimation) 
		_animationRepeatCounter += 1;

	// Once we reach the max number of repeat for one animation, we move to the next one
	if (_animationRepeatCounter > ANIMATION_COUNTER_MAX)
	{
		_animationRepeatCounter = 0;
		NextAnimation();
	}		
}

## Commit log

2019-07-21 Creation
2019-07-21 Clean up EEPROM-AT28C16-PROGRAMMER
2019-07-21 added back EEPROM-AT28C16-PROGRAMMER
2019-07-21 New board Useless USB Gift Board
2019-07-27 New board Nusbio WaveShare SeedStudio edition larger with 8 blue 1206 led
2019-08-05 board 4017-7Segment v2 on hold, until I received chip 4017B
2019-08-07 Create v2 of Useless USB Gift Board, large board made by seeedstudio
2019-08-13 Created 4017-7Segment v2
2019-08-18 Update 4017-7Segment
2019-08-18 Update 0 TO 9 Counter 74LS90
2019-08-19 Update/create Clock Module Time 555 -Simplified
2019-08-23 Change png file of some board for fredericTorres.com website
2019-08-30 Prepare for shipping to seeedstudio manufacturing '0 TO 9 Counter 74LS90'
2019-08-30 Prepare for shipping to seeedstudio manufacturing
2019-09-02 Add bitly.com reference to some board
2019-09-14 fix bug in pcb '0 TO 9 Counter 74LS90'
2019-09-25 Create fCPU
2019-09-26 Update fCPU, add second register
2019-09-27 Added Clock Multiplexer pcb
2019-09-28 Update fCPU
2019-10-03 Added old pcb deleted by accident
2019-10-03 removed un-needed files
2019-10-04 update clock multiplexer
2019-10-07 Research on ATTINY85 programming
2019-10-12 Write firmware for Usb Business Card
2019-10-13 Create/update PCBfor Usb Business Card
2019-10-17 Update firmware for Usb Business Card
2019-11-19 Deploy UsbBusiness card to arduino uno mini on real pcb
2019-11-24 Add fCPU_Controller source code
2019-12-07 Verify bug fix for '0 TO 9 Counter 74LS90' board
2019-12-15 Revisit One Led Blinker pcb
2019-12-15 Create UpTo11
2019-12-15 Create UpTo11 Front Panel
2019-12-18 Create new clock module SMD
2019-12-22 Fix bug in 4017-7Segment v2
2019-12-22 Fix bugs in UpTo11, 2 baord
2019-12-23 Create v2 of USB Mutiplicator, make the board larger and 6 usb out
2019-12-27 Create v3 of 0 to 99 counter
2019-12-28 Create USB multiplicator v2 big
2019-12-28 Create v2 of Clock de-multiplexer
2019-12-28 Turn clock smd into a mounting pcb on top of a main pcb
2020-01-12 Fix bug in clock multi plexer
2020-02-03 CReate CheetahBooster
2020-02-15 Update cheetah booster
2020-03-01 Update Test Diode SMD
2020-03-11 Update CheetahBoosyer v2
2020-03-16 Create CheetahBooster MCU
2020-03-16 Add Cheetah Booster Firmware
2020-04-23 Update CheetahBooster
2020-08-19 Update for v1

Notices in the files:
parts and their libraries:
SparkFun-DigitalIC: Licensing: Creative Commons ShareAlike 4.0 International - https://creativecommons.org/licenses/by-sa/4.0
microbuilder: This work is placed in the public domain, and may be freely used for commercial and non-commercial work with the following conditions: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
